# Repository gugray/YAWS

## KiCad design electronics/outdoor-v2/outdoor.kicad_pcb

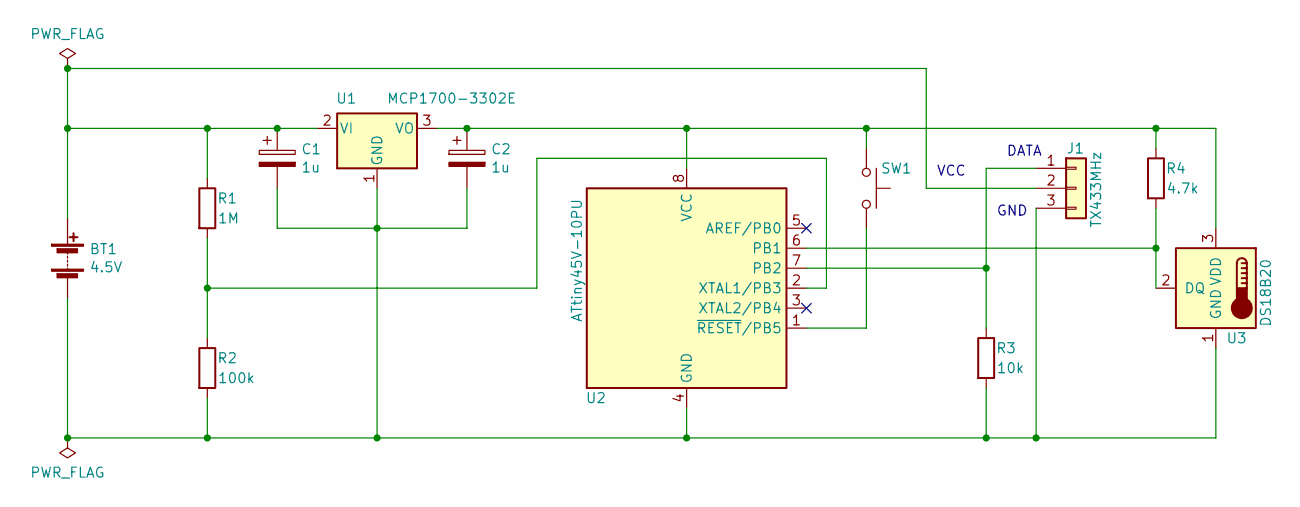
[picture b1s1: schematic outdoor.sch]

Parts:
BT1: 4.5V; PinHeader_1x02_P2.54mm_Vertical
C1, C2: 1u; C_Rect_L7.0mm_W2.5mm_P5.00mm
J1: TX433MHz; PinHeader_1x03_P2.54mm_Vertical
R1: 1M; R_Axial_DIN0207_L6.3mm_D2.5mm_P10.16mm_Horizontal
R2: 100k; R_Axial_DIN0207_L6.3mm_D2.5mm_P10.16mm_Horizontal
R3: 10k; R_Axial_DIN0207_L6.3mm_D2.5mm_P10.16mm_Horizontal
R4: 4.7k; R_Axial_DIN0207_L6.3mm_D2.5mm_P10.16mm_Horizontal
SW1: SW_Push; SW_PUSH_6mm
U1: MCP1700-3302E; TO-92_Inline_Wide
U2: ATtiny45V-10PU; DIP-8_W7.62mm
U3: DS18B20; TO-92_Inline_Wide

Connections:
unnamed: BT1.1 (+), C1.1, J1.2, R1.1, U1.2 (VI)
unnamed: BT1.2 (-), C1.2, C2.2, J1.3, R2.2, R3.2, U1.1 (GND), U2.4 (GND), U3.1 (GND)
unnamed: C2.1, R4.1, SW1.1, U1.3 (VO), U2.8 (VCC), U3.3 (VDD)
unnamed: J1.1, R3.1, U2.7 (PB2)
unnamed: R1.2, R2.1, U2.2 (XTAL1/PB3)
unnamed: R4.2, U2.6 (PB1), U3.2 (DQ)
unnamed: SW1.2, U2.1 (~RESET~/PB5)

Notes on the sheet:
VCC
DATA
GND

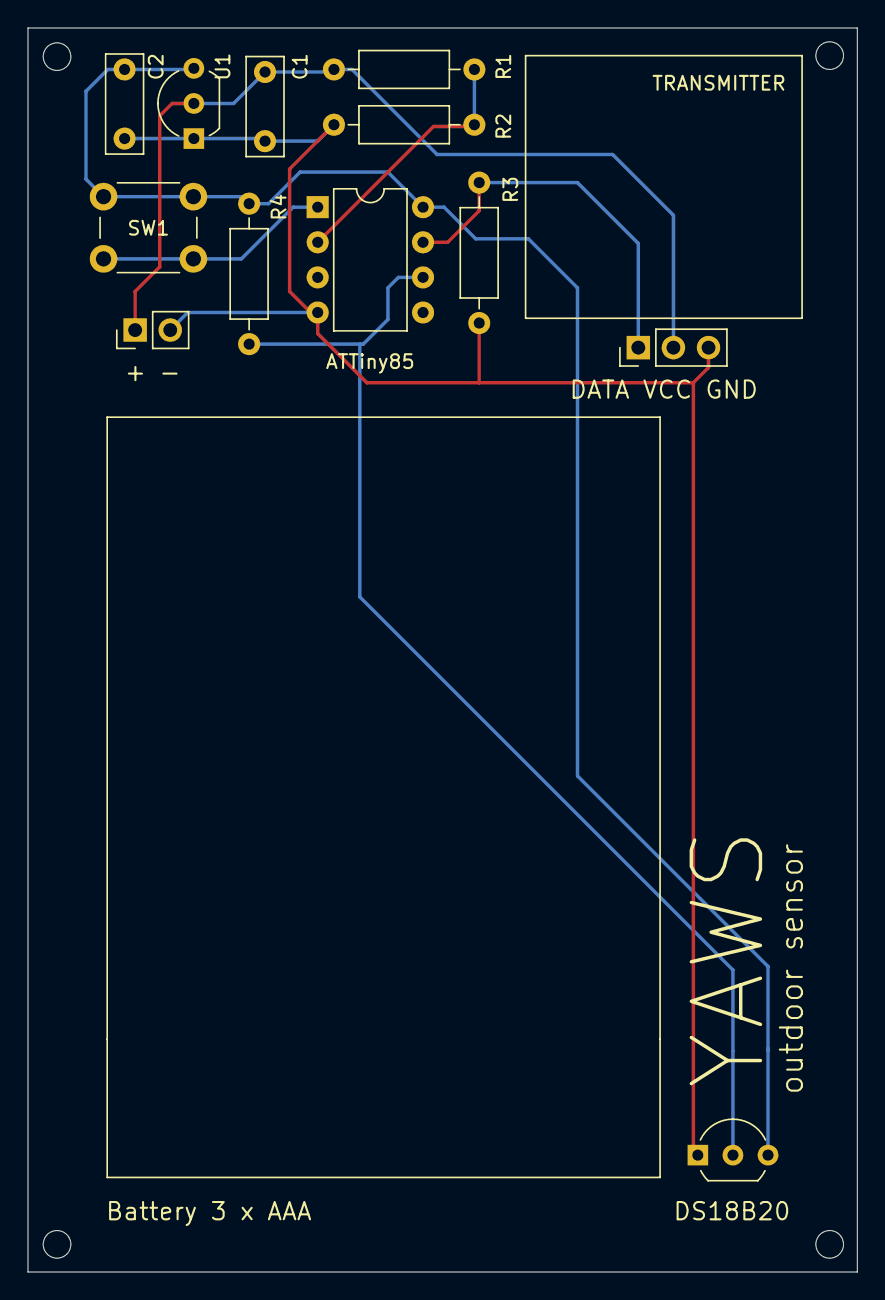
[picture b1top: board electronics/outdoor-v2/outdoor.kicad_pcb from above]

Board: 2 copper layers, 60.0 x 90.0 mm, 12 parts (0 on the bottom side), 7 nets.

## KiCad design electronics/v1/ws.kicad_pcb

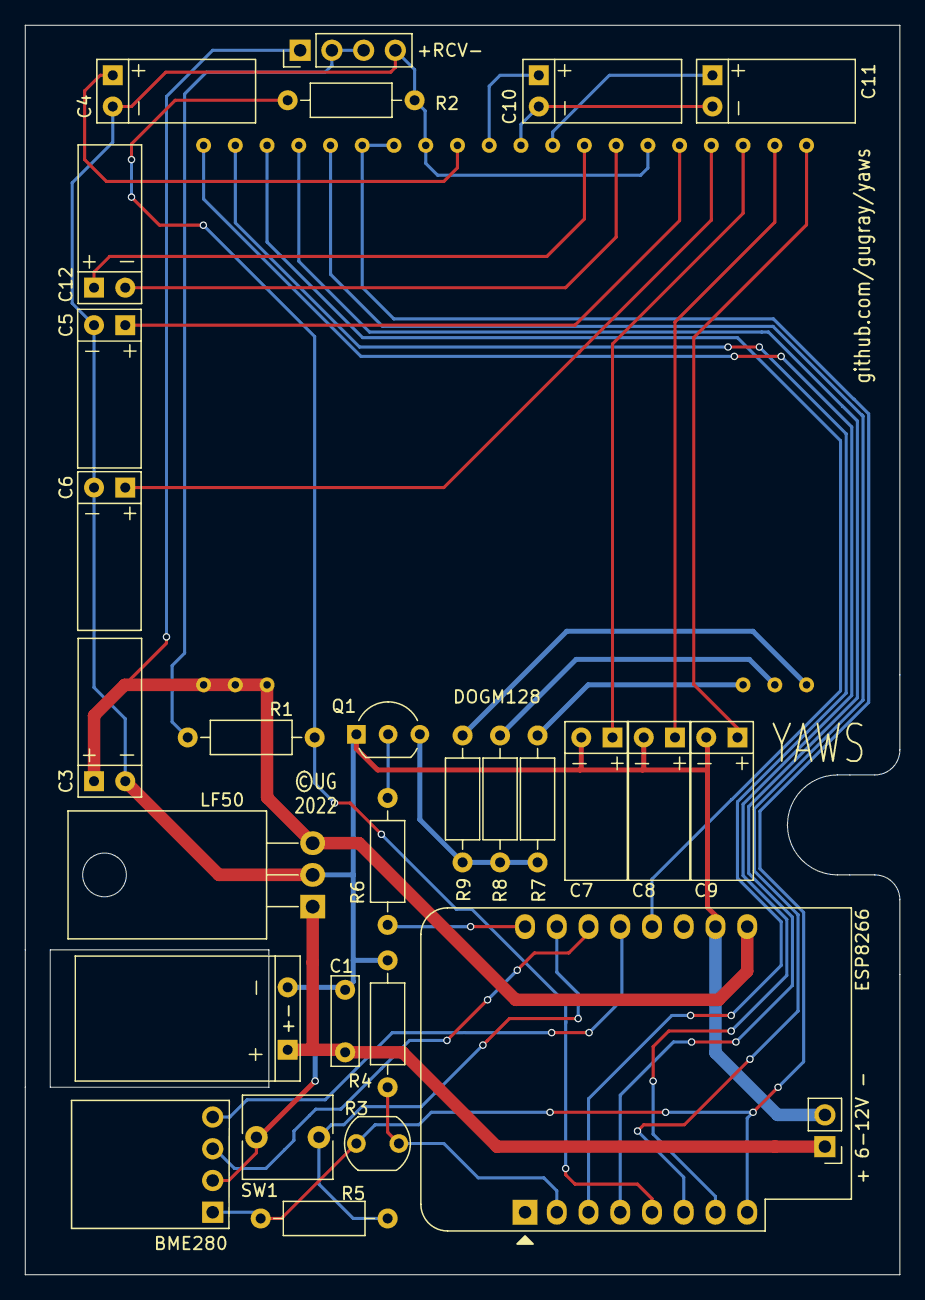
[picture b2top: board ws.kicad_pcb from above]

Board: 2 copper layers, 70.0 x 100.0 mm, 29 parts (0 on the bottom side), 32 nets.

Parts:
+ 6-12V -: PWR; PinHeader_1x02_P2.54mm_Vertical
+-: 1000uF; CP_Radial_D10.0mm_L18mm_P5.0mm_Lying
+RCV-: Recevier; PinHeader_1x04_P2.54mm_Vertical
BME280: BME280_I2C_Board; BME280_Board
C1: .1uF; C_Rect_L7.0mm_W2.0mm_P5.00mm
C3: 2.2uF; CP_Radial_D5.0mm_L10mm_P2.50mm_Lying
C4, C5, C6, C7, C8, C9, C10, C11, C12: CP; CP_Radial_D5.0mm_L10mm_P2.50mm_Lying
DOGM128: EA-DOGM128W-6; DOGM128
ESP8266: WeMos_D1_mini; WEMOS_D1_mini_light
LF50: LF50_TO220; TO-220-3_Horizontal_TabDown
Q1: TN0604G; TO-92_Inline_Wide
R1: 47k; R_Axial_DIN0207_L6.3mm_D2.5mm_P10.16mm_Horizontal
R2: 65k; R_Axial_DIN0207_L6.3mm_D2.5mm_P10.16mm_Horizontal
R3: GL5516; R_LDR_5.1x4.3mm_P3.4mm_Vertical
R4: 5k; R_Axial_DIN0207_L6.3mm_D2.5mm_P10.16mm_Horizontal
R5: 10k; R_Axial_DIN0207_L6.3mm_D2.5mm_P10.16mm_Horizontal
R6, R7, R8, R9: 100R; R_Axial_DIN0207_L6.3mm_D2.5mm_P10.16mm_Horizontal
SW1: SW_Push; C_Rect_L7.0mm_W6.5mm_P5.00mm

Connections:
3V3: BME280.1, DOGM128.34, DOGM128.35, ESP8266.8, R3.1, R5.2
5V0: +RCV-.1, C3.1, DOGM128.1, DOGM128.2, DOGM128.3, ESP8266.9, LF50.3
A0: ESP8266.2, R3.2, R4.1
D0: DOGM128.39, ESP8266.3
D1: BME280.3, ESP8266.14
D2: BME280.4, ESP8266.13
D3: DOGM128.38, ESP8266.12
D5: DOGM128.37, ESP8266.4
D6: ESP8266.5, R1.2, R2.1
D7: DOGM128.36, ESP8266.6
D8: DOGM128.40, ESP8266.7
GND: + 6-12V -.2, +-.2, +RCV-.4, BME280.2, C1.2, C3.2, C4.2, C5.2, C6.2, C7.2, C8.2, C9.2, DOGM128.26, DOGM128.33, ESP8266.10, LF50.2, Q1.1, R2.2, R4.2, SW1.1
unnamed: + 6-12V -.1, +-.1, C1.1, LF50.1
unnamed: C4.1, DOGM128.32
unnamed: C5.1, DOGM128.25
unnamed: C6.1, DOGM128.24
unnamed: C7.1, DOGM128.23
unnamed: C8.1, DOGM128.22
unnamed: C9.1, DOGM128.21
unnamed: C10.1, DOGM128.31
unnamed: C10.2, C11.2, DOGM128.30
unnamed: C11.1, DOGM128.29
unnamed: C12.1, DOGM128.28
unnamed: C12.2, DOGM128.27
unnamed: +RCV-.2, +RCV-.3, R1.1
unnamed: Q1.2, R6.2
unnamed: Q1.3, R7.1, R8.1, R9.1
unnamed: DOGM128.18, R7.2
unnamed: DOGM128.19, R8.2
unnamed: DOGM128.20, R9.2
RX: ESP8266.15, R5.1, SW1.2
TX: ESP8266.16, R6.1

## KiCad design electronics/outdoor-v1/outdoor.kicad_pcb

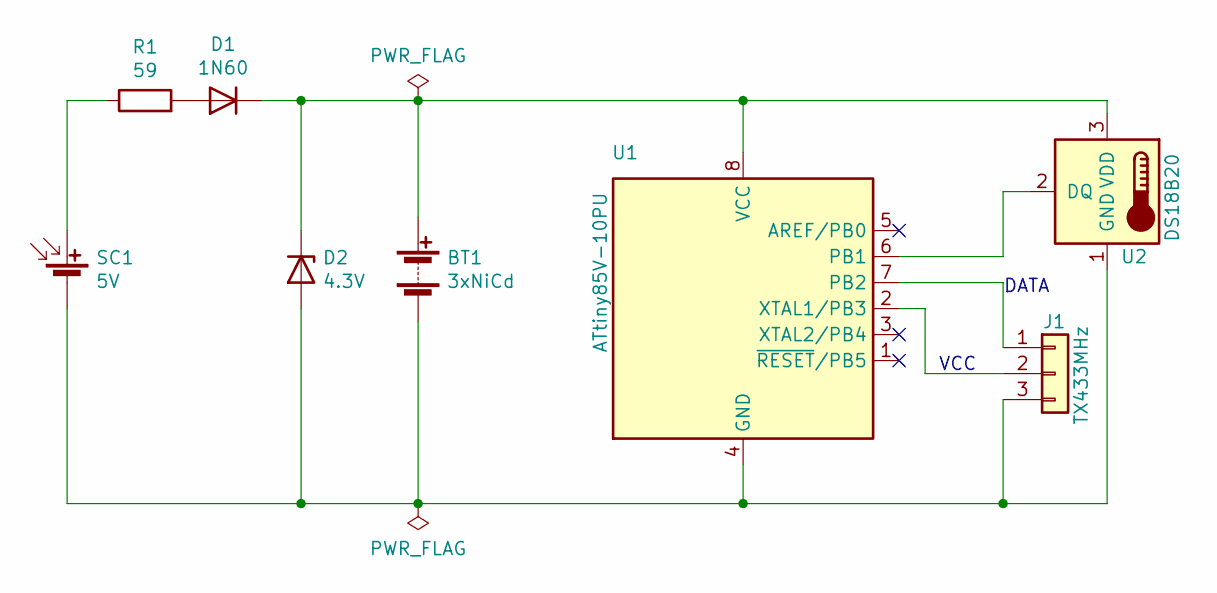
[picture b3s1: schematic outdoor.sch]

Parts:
BT1: 3xNiCd; NiCd-Small
D1: 1N60; D_DO-35_SOD27_P10.16mm_Horizontal
D2: 4.3V; D_DO-35_SOD27_P10.16mm_Horizontal
J1: TX433MHz; PinHeader_1x03_P2.54mm_Vertical
R1: 59; R_Axial_DIN0207_L6.3mm_D2.5mm_P10.16mm_Horizontal
SC1: 5V; PinHeader_1x02_P2.54mm_Vertical
U1: ATtiny85V-10PU; DIP-8_W7.62mm
U2: DS18B20; TO-92_Inline_Wide

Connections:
unnamed: BT1.1 (+), D1.1 (K), D2.1 (K), U1.8 (VCC), U2.3 (VDD)
unnamed: BT1.2 (-), D2.2 (A), J1.3, SC1.2 (-), U1.4 (GND), U2.1 (GND)
unnamed: D1.2 (A), R1.2
unnamed: J1.1, U1.7 (PB2)
unnamed: J1.2, U1.2 (XTAL1/PB3)
unnamed: R1.1, SC1.1 (+)
unnamed: U1.6 (PB1), U2.2 (DQ)

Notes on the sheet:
VCC
DATA

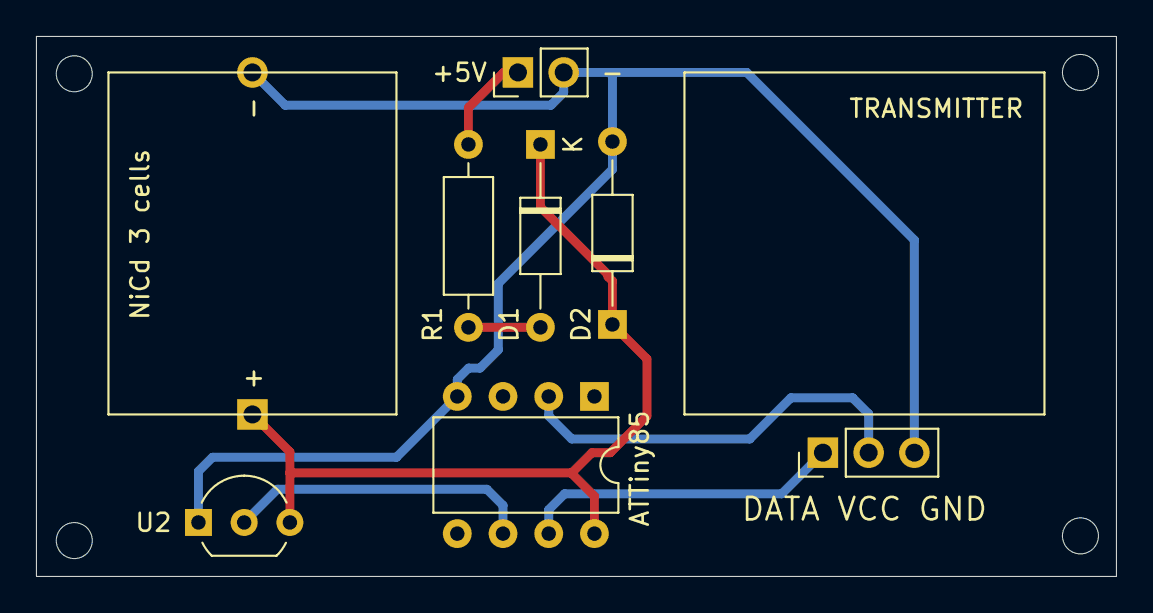
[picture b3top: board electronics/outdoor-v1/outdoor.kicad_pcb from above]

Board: 2 copper layers, 60.0 x 30.0 mm, 8 parts (0 on the bottom side), 7 nets.

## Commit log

2022-08-08 electronics first draft
2022-08-08 empty code skeleton
2022-08-08 verifying peripherals
2022-08-09 schematic update
2022-08-09 file system; download over https; update from downloaded file
2022-08-10 got radio working; verified backlight
2022-08-10 read brightness; read bme
2022-08-13 designed PCB
2022-08-13 training weather predictor WIP
2022-08-14 pcb sent for fabrication
2022-08-17 more (failed) experiments with NN prediction
2022-08-17 cleanup after abandoned weather predictor approach
2022-08-19 30-pixel digits; rule-based predictor
2022-08-22 display design WIP; custom fonts
2022-08-23 14px font and weather icons
2022-08-23 schematic correction (R4 exact value)
2022-08-23 refactoring towards final firmware
2022-08-28 config/update server WIP
2022-08-28 case first design
2022-08-28 move letter design files
2022-08-29 case design update
2022-08-29 trend arrows; revised prediction algo
2022-08-29 OTA update via WiFi access point
2022-08-31 last touches & fixes
2022-12-18 outdoor unit WIP (basically working)
2022-12-19 outdoor unit dialed in
2022-12-19 outdoor schematic v2 with necessary changes; PCB still needs update
2023-01-29 outdoor unit revision WIP
2023-02-19 new outdoor board

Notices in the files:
electronics/v1/ws.kicad_pcb:
©UG
